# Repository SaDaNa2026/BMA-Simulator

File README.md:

# Hardware

Die Steuerung des BMA-SImulators ist dafür ausgelegt, auf einem Raspberry Pi ausgeführt zu werden. 
Getestet wurde mit einem Raspberry Pi 5B mit 8 GB RAM, die Anwendung sollte allerdings auch ohne Probleme 
auf einem Modell 4 mit 2 GB RAM laufen.

FAT und FBF werden durch den Raspberry Pi über 5V, 3.3V und GND mit Strom versorgt 
und per I2C über die serielle Schnittstelle angesteuert. 
Die Platinen können anhand der beiliegenden KiCAD-Dateien hergestellt werden. 
Zusatzmodule wie eine Blitzleuchte, ein Freischaltelement oder physische Melder können nach Belieben hinzugefügt 
und in die Steuerung eingebunden oder deaktiviert werden.

# Software

## Abhängigkeiten

Zum Ausführen des Python-Scripts müssen Python 3.13 oder neuer und alle in requirements.txt 
definierten Abhängigkeiten installiert sein. 

Bei der Installation der lgpio-Bibliothek ist zu beachten, dass dafür lg auf dem System installiert sein muss. 
lg und die dazugehörige Installationsanleitung sind unter https://github.com/joan2937/lg zu finden.

Auch pygobject benötigt diverse systemweite Bibliotheken, darunter libcairo2-dev und libgtk-4-dev. Die Fehlermeldungen 
bei der Installation sind in der Regel sehr hilfreich, um fehlende Pakete zu identifizieren.

Zusätzlich ist Okular notwendig, um die Hilfedatei anzeigen zu können. Dabei muss okular-extra-backends installiert werden, 
um Markdown-Dateien anzeigen zu können. Natürlich kann auch ein anderer Markdown-Viewer verwendet werden, 
wenn in Application.py die Konstante MARKDOWN_VIEWER entsprechend angepasst wird.  
Falls die Hilfedatei nach PDF konvertiert wird, bieten sich noch mehr Möglichkeiten für die Anzeige. 
Markdown wurde lediglich aufgrund der besseren Integration in das Versionskontrollsystem ausgewählt.

## Desktopeintrag

Es liegt ein Beispiel für eine passende Desktopeintrags-Datei bei. Wenn die in der Datei angegebenen Anpassungen 
erfolgt sind, kann die Datei im entsprechenden Ordner (z.B. /usr/local/share/applications/) abgelegt werden.  
Falls ein Autostart der App erwünscht ist, kann der Desktopeintrag zusätzlich noch in /etc/xdg/autostart/ abgelegt werden.

## Startskript

Da sich alle Python-Pakete und Skripte in einer virtuellen Umgebung befinden, muss diese beim Programmstart erst 
aktiviert werden. Daher ist ein Startskript nötig, das diese Aufgabe übernimmt. Ein entsprechendes Beispiel liegt bei, 
es muss nur der Pfad zum Anwendungsordner angepasst werden. Das Skript kann dann z.B. in /usr/local/bin abgelegt werden.

Für den Fall, dass alle Python-Pakete systemweit installiert sind (ohne virtuelle Umgebung), 
entfällt die Notwendigkeit des Startskripts. Man verliert dann aber natürlich auch alle Vorteile 
der Separierung durch virtuelle Umgebungen.

## Konfiguration von labwc

Falls Raspberry Pi OS (oder ein anderes Betriebssystem mit labwc als Compositor) verwendet wird, 
sollten für ein einheitliches Design der Anwendung Client-Side-Decorations bevorzugt werden. 
Dazu muss in der labwc-Konfigurationsdatei (in der Regel /etc/xdg/labwc/rc.xml) 
die Variable <core><decorations> auf client gesetzt werden. 
Weitere Informationen dazu sind unter https://labwc.github.io/labwc-config.5.html#entry_core_decoration zu finden.  
In diesem Fall empfiehlt es sich auch, in /etc/xdg/labwc/environment die Umgebungsvariable 
QT_WAYLAND_DISABLE_WINDOWDECORATION=0 zu setzen, da ansonsten für Qt-Anwendungen wie Okular 
keine Kopfleiste mehr angezeigt wird.

## Konstanten

In Application.py werden unterhalb der Imports einige Konstanten definiert, mit denen die Anwendung 
an die Umgebung angepasst werden kann. Verfügbar sind:

- Der Standard-Dateipfad für das Öffnen und Speichern von Dateien. Der Pfad sollte existieren, 
    andernfalls funktioniert die Anwendung aber trotzdem.
- Der Markdown-Viewer zur Anzeige der Hilfedatei (einzutragender Name entspricht dem in der Shell).
- Die Standard-Gebäudebeschreibung. Der Zeilenumbruch ist mit \n zu setzen. Die maximale Länge 
    einer Zeile beträgt 20 Zeichen.
- Eine PIN, mit der potenziell destruktive Aktionen wie Speichern oder Rollback gesichert werden. 
    Dies bietet ganz ausdrücklich keine wirkliche Sicherheit, sondern soll nur gegen Fehlbedienung absichern.
- Ein Tupel aller physischen Melder, die angeschlossen sind. Kommentar im Code beachten!  
    Falls keine physischen Melder vorhanden sind, können alle Einträge bis auf den Melder mit Nummer 0/1, 
    welcher intern als Repräsentation der Löschanlage notwendig ist, entfernt werden.
- GPIO-Pin des Relais' für die Blitzleuchte, kann hier auch abgeschaltet werden.

## Integration von Git

Um den Dateistand zurücksetzen zu können, ist Git als Versionskontrollsystem integriert. Bei jedem Speichern
einer Gebäudekonfiguration oder eines Szenarios wird im entsprechenden Verzeichnis ein Repository initialisiert,
falls es nicht bereits eines ist. Anschließend werden alle Änderungen gestaget und committet. 
Über die Funktion "Dateistand zurücksetzen" gibt es dann die Möglichkeit, einen Hard Reset durchzuführen. 
Natürlich ist auch eine manuelle Verwaltung des Repositorys mithilfe von Git möglich.

Diese Integration macht einige Annahmen, die erfüllt werden sollten, um unerwünschte Folgen zu vermeiden:

- Für jede Gebäudekonfiguration mitsamt den dazugehörigen Szenarien existiert ein eigenes Verzeichnis (Gebäudeverzeichnis).
   Dabei können für Szenario-Dateien beliebig viele Unterverzeichnisse mit beliebiger Verschachtelung angelegt werden.
   In diesen Unterverzeichnissen dürfen jedoch keine Gebäudeverzeichnisse enthalten sein, denn:
- Gebäudeverzeichnisse dürfen nicht verschachtelt werden: Dadurch werden alle Änderungen im höhergeordneten Verzeichnis
   der beiden committet, wodurch keine saubere Trennung der Gebäude in den Commit-Messages mehr existiert.
- Es sollte ein eigenes Verzeichnis angelegt werden, das alle Gebäudeverzeichnisse bzw. Verzeichnisse 
   von Gebäudeverzeichnissen enthält. Dieses Verzeichnis sollte der Konstante DEFAULT_FILE_PATH 
   in Application.py entsprechen, wodurch sich die Öffnen- und Speicher-Dialoge direkt im richtigen Verzeichnis befinden.  
   Die Abschottung verhindert, dass andere, "unbeteiligte" Dateien in das Repository 
   aufgenommen werden oder ein Repository in einem Verzeichnis initialisiert wird, wo dies unerwünscht ist.

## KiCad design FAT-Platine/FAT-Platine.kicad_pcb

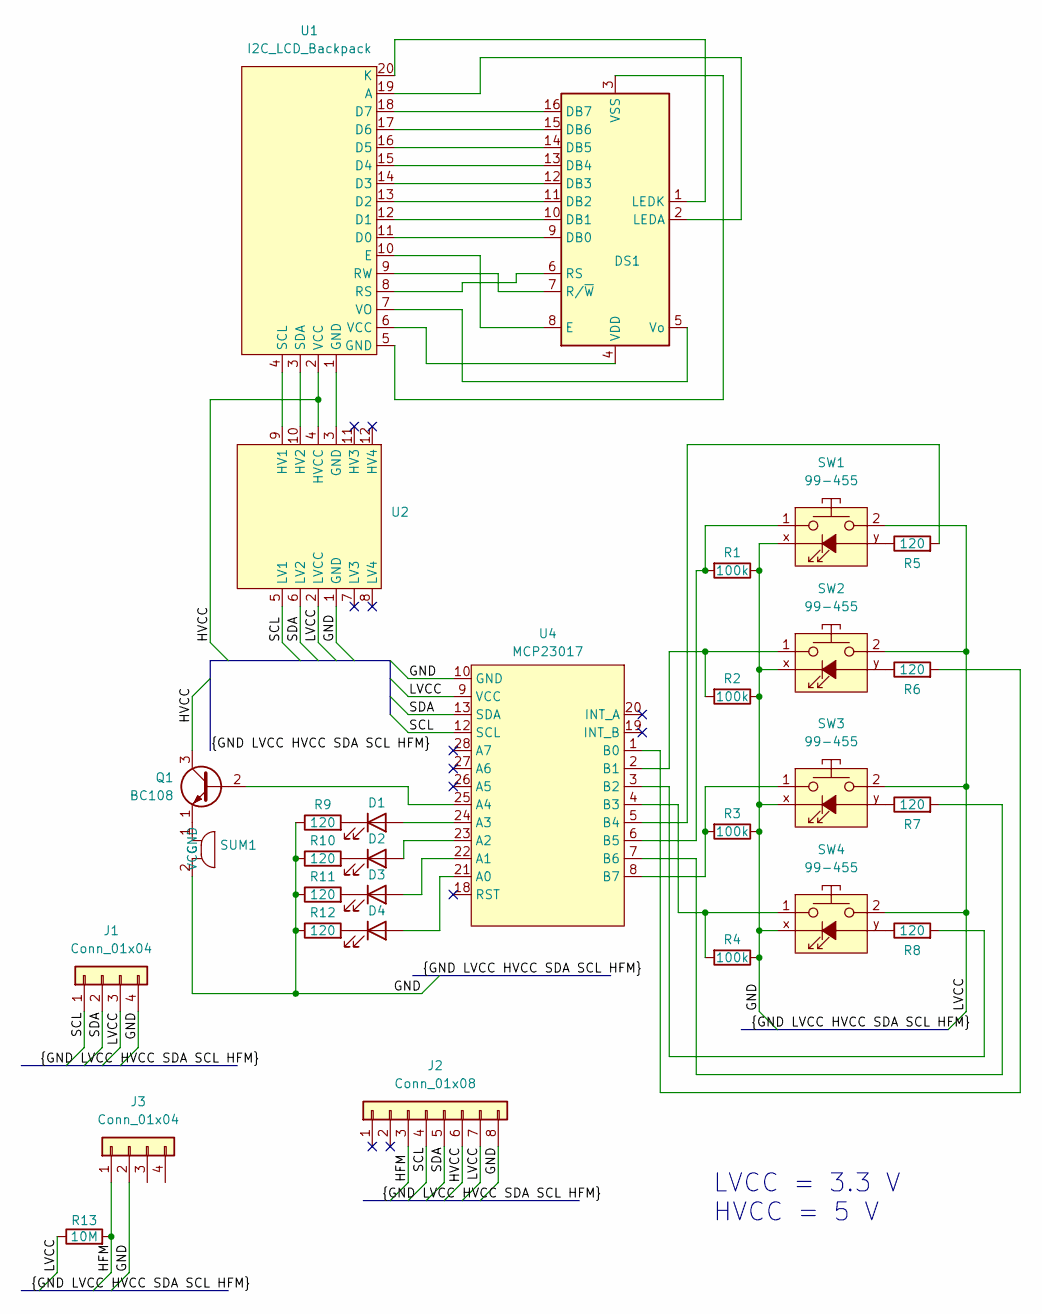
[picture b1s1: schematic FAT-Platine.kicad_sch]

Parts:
D1, D2, D3, D4: LED; LED_D5.0mm
DS1: HD44780; LCD 4x20
J1, J3: Conn_01x04; WAGO_236-404
J2: Conn_01x08; WAGO_236-408
Q1: BC108; TO-18-3
R1, R2, R3, R4: 100k; R_Axial_DIN0207_L6.3mm_D2.5mm_P10.16mm_Horizontal
R5, R6, R7, R8, R9, R10, R11, R12: 120; R_Axial_DIN0207_L6.3mm_D2.5mm_P10.16mm_Horizontal
R13: 10M; R_Axial_DIN0207_L6.3mm_D2.5mm_P10.16mm_Horizontal
SUM1: AL-60SP05
SW1, SW2, SW3, SW4: 99-455; Switch_EAO_4-pin
U1: I2C_LCD_Backpack; LCD_I2C_Backpack
U2: Logic_Level_Converter
U4: MCP23017; MCP23017_Breakout

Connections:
/GND: J1.4, J2.8, J3.2, R1.1, R2.1, R3.1, R4.1, R9.1, R10.1, R11.1, R12.1, SUM1.2 (GND), SW1.x, SW2.x, SW3.x, SW4.x, U2.1 (GND), U4.10 (GND)
/HFM: J2.3, J3.1, R13.2
/HVCC: J2.6, Q1.3 (C), U1.2 (VCC), U2.4 (HVCC)
/LVCC: J1.3, J2.7, R13.1, SW1.2, SW2.2, SW3.2, SW4.2, U2.2 (LVCC), U4.9 (VCC)
/SCL: J1.1, J2.4, U2.5 (LV1), U4.12 (SCL)
/SDA: J1.2, J2.5, U2.6 (LV2), U4.13 (SDA)
unnamed: D1.2 (A), U4.24 (A3)
unnamed: D1.1 (K), R9.2
unnamed: D2.2 (A), U4.23 (A2)
unnamed: D2.1 (K), R10.2
unnamed: D3.2 (A), U4.22 (A1)
unnamed: D3.1 (K), R11.2
unnamed: D4.2 (A), U4.21 (A0)
unnamed: D4.1 (K), R12.2
unnamed: DS1.9 (DB0), U1.11 (D0)
unnamed: DS1.10 (DB1), U1.12 (D1)
unnamed: DS1.11 (DB2), U1.13 (D2)
unnamed: DS1.12 (DB3), U1.14 (D3)
unnamed: DS1.13 (DB4), U1.15 (D4)
unnamed: DS1.14 (DB5), U1.16 (D5)
unnamed: DS1.15 (DB6), U1.17 (D6)
unnamed: DS1.16 (DB7), U1.18 (D7)
unnamed: DS1.8 (E), U1.10 (E)
unnamed: DS1.2 (LEDA), U1.19 (A)
unnamed: DS1.1 (LEDK), U1.20 (K)
unnamed: DS1.6 (RS), U1.8 (RS)
unnamed: DS1.7 (R/~W), U1.9 (RW)
unnamed: DS1.4 (VDD), U1.6 (VCC)
unnamed: DS1.3 (VSS), U1.5 (GND)
unnamed: DS1.5 (Vo), U1.7 (VO)
unnamed: Q1.2 (B), U4.25 (A4)
unnamed: Q1.1 (E), SUM1.1 (VCC)
unnamed: R5.1, SW1.y
unnamed: R6.1, SW2.y
unnamed: R7.1, SW3.y
unnamed: R8.1, SW4.y
unnamed: U1.1 (GND), U2.3 (GND)
unnamed: U1.4 (SCL), U2.9 (HV1)
unnamed: U1.3 (SDA), U2.10 (HV2)
unnamed: R6.2, U4.1 (B0)
unnamed: R2.2, SW2.1, U4.2 (B1)
unnamed: R8.2, U4.3 (B2)
unnamed: R4.2, SW4.1, U4.4 (B3)
unnamed: R5.2, U4.5 (B4)
unnamed: R1.2, SW1.1, U4.6 (B5)
unnamed: R7.2, U4.7 (B6)
unnamed: R3.2, SW3.1, U4.8 (B7)

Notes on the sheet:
LVCC = 3.3 V HVCC = 5 V

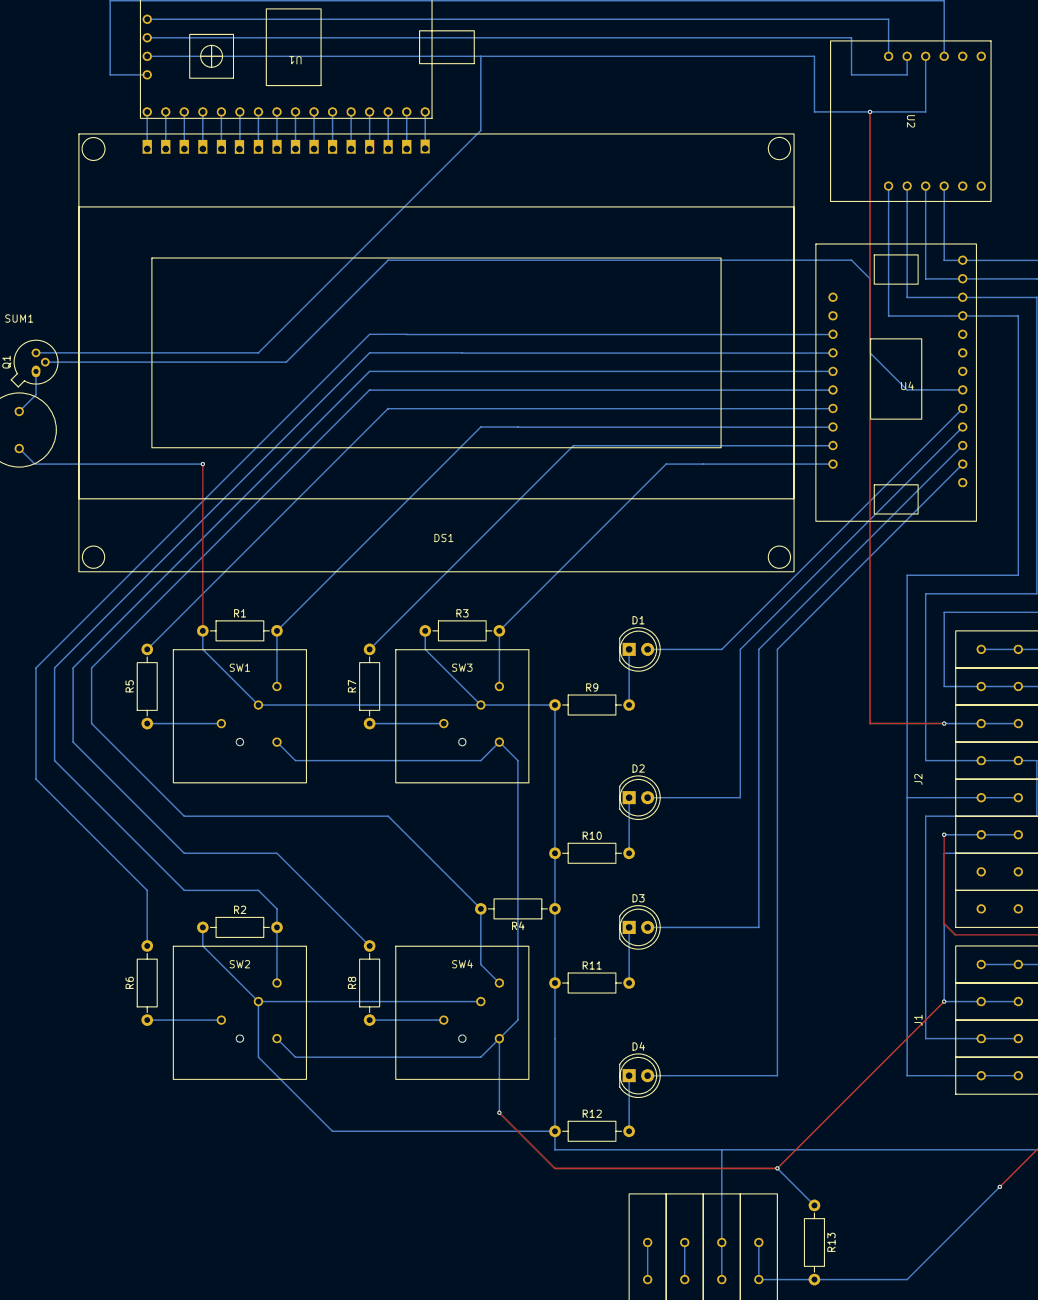
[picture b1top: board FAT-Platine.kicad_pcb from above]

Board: 2 copper layers, 30 parts (0 on the bottom side), 47 nets.

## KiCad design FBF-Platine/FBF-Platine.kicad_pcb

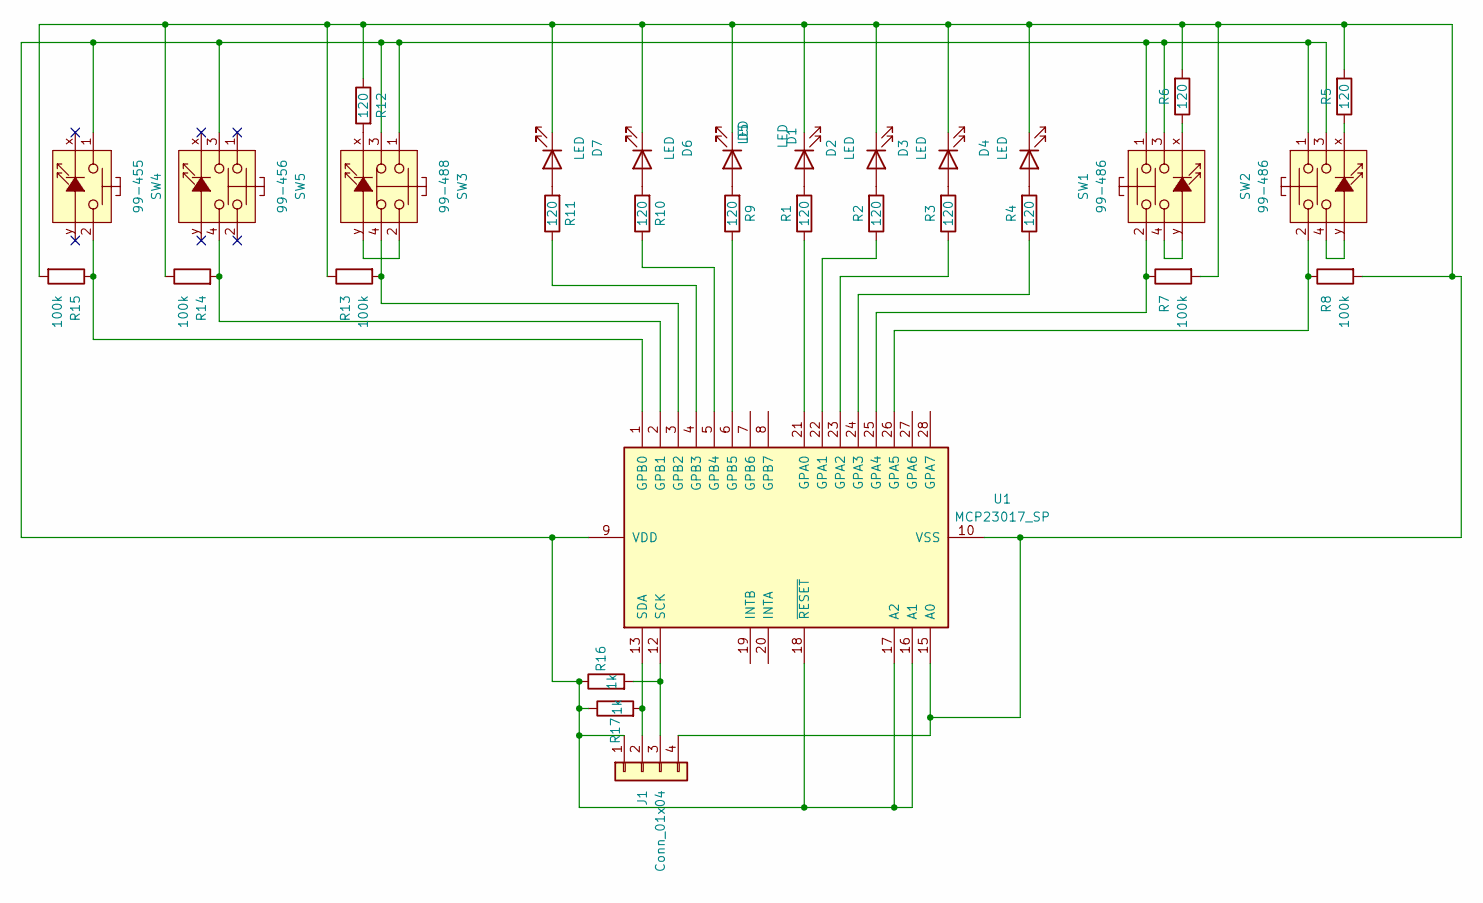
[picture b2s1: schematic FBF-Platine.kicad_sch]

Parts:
D1, D2, D3, D4, D5, D6, D7: LED; LED_D5.0mm
J1: Conn_01x04; WAGO_236-404
R1, R2, R3, R4, R5, R6, R9, R10, R11, R12: 120; R_Axial_DIN0207_L6.3mm_D2.5mm_P10.16mm_Horizontal
R7, R8, R13, R14, R15: 100k; R_Axial_DIN0207_L6.3mm_D2.5mm_P10.16mm_Horizontal
R16, R17: 1k; R_Axial_DIN0207_L6.3mm_D2.5mm_P10.16mm_Horizontal
SW1, SW2: 99-486; Switch_EAO_6-pin
SW3: 99-488; Switch_EAO_6-pin
SW4: 99-455; Switch_EAO_4-pin
SW5: 99-456; Switch_EAO_6-pin
U1: MCP23017_SP; DIP-28_W7.62mm

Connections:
unnamed: D1.2 (A), R1.2
unnamed: D1.1 (K), D2.1 (K), D3.1 (K), D4.1 (K), D5.1 (K), D6.1 (K), D7.1 (K), J1.4, R5.2, R6.2, R7.2, R8.2, R12.1, R13.1, R14.1, R15.2, U1.10 (VSS), U1.15 (A0)
unnamed: D2.2 (A), R2.2
unnamed: D3.2 (A), R3.2
unnamed: D4.2 (A), R4.2
unnamed: D5.2 (A), R9.2
unnamed: D6.2 (A), R10.2
unnamed: D7.2 (A), R11.2
unnamed: J1.1, R16.1, R17.1, SW1.1, SW1.3, SW2.1, SW2.3, SW3.1, SW3.3, SW4.1, SW5.3, U1.9 (VDD), U1.16 (A1), U1.17 (A2), U1.18 (~RESET)
unnamed: J1.2, R17.2, U1.13 (SDA)
unnamed: J1.3, R16.2, U1.12 (SCK)
unnamed: R5.1, SW2.x
unnamed: R6.1, SW1.x
unnamed: R12.2, SW3.x
unnamed: SW1.4, SW1.y
unnamed: SW2.4, SW2.y
unnamed: SW3.2, SW3.y
unnamed: R1.1, U1.21 (GPA0)
unnamed: R2.1, U1.22 (GPA1)
unnamed: R3.1, U1.23 (GPA2)
unnamed: R4.1, U1.24 (GPA3)
unnamed: R7.1, SW1.2, U1.25 (GPA4)
unnamed: R8.1, SW2.2, U1.26 (GPA5)
unnamed: R15.1, SW4.2, U1.1 (GPB0)
unnamed: R14.2, SW5.4, U1.2 (GPB1)
unnamed: R13.2, SW3.4, U1.3 (GPB2)
unnamed: R11.1, U1.4 (GPB3)
unnamed: R10.1, U1.5 (GPB4)
unnamed: R9.1, U1.6 (GPB5)

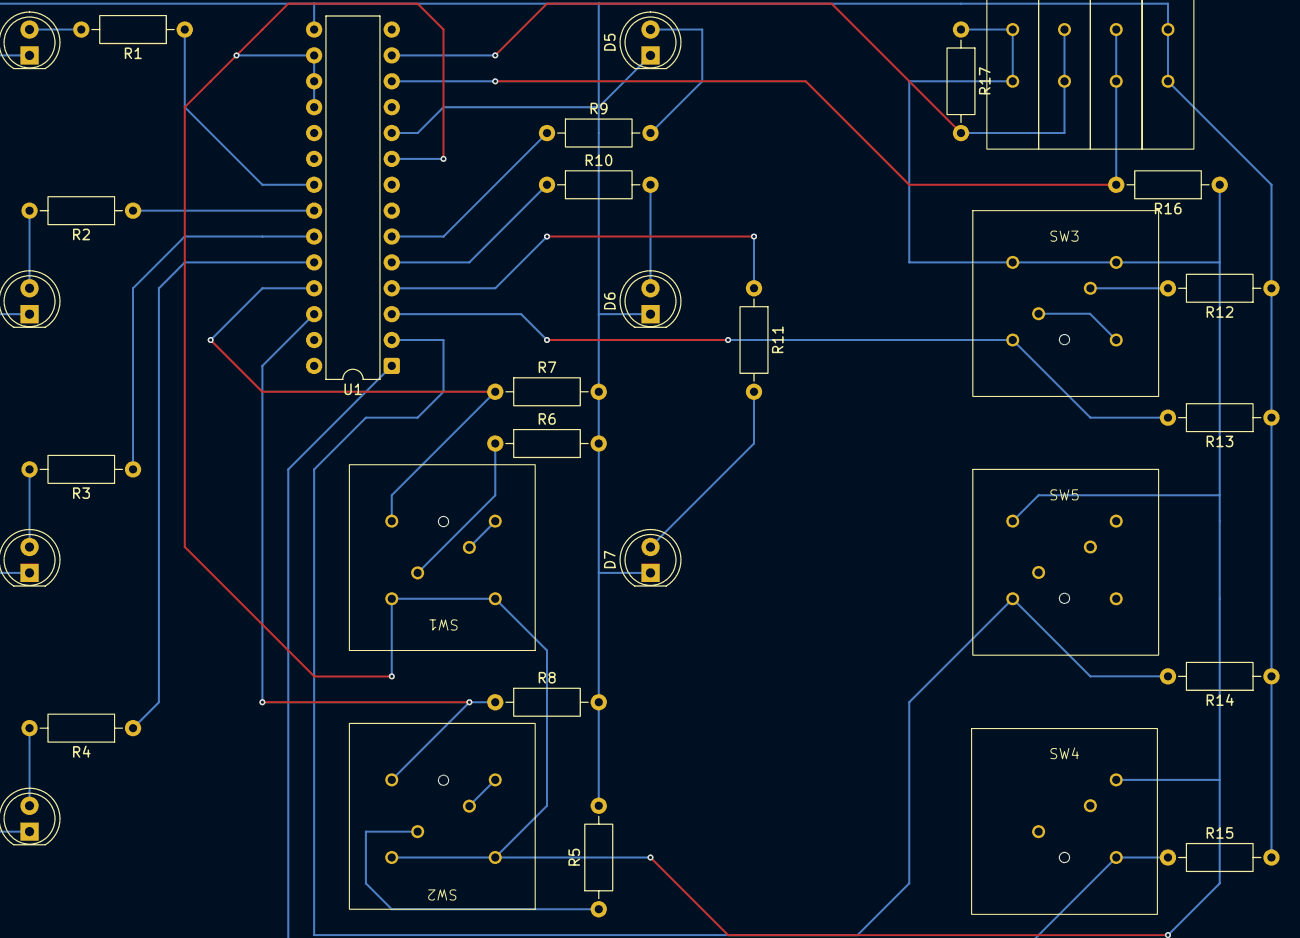
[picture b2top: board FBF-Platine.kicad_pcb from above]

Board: 2 copper layers, 31 parts (0 on the bottom side), 29 nets.

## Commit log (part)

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2025-11-03 Sehr frühe, experimentelle Testversion zum Management von Meldern als Klassen und der dynamischen Erstellung von Meldern.
2025-11-04 Melderlinien und Melder werden nun in einem dictionary gespeichert, sodass jedes Objekt mit der Nummer der Melderlinie und des Melders aufgerufen werden kann. Es können dadurch auch arbiträre Melder(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
2025-11-05 Funktionalität zum Speichern und Öffnen wurde vorerst entfernt. Die neue Klassse Building für Eigenschaften des Gebäudes wrde hinzugefügt. Eigenschaften und Zugehörigkeiten werden nicht mehr in einem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
2025-11-06 Refactoring: Alle globalen Funktionen wurden in die Klasse MainWindow verschoben. Die Klasse und Funktionen für den Öffnen-Dialog wurden logischer benannt.
    Fix: Beim Laden aus der Datei wurden in building.circuit_dict bisher strings für die keys geschrieben, was das Löschen unmöglich machte. Nun werden die keys korrekt als integer geschrieben.
2025-11-24 Ein Bug wurde entfernt, durch den bei jedem Öffnen des Kontextmenüs der delete_circuit_button erneut mit der entsprechenden Funktion verbunden wurde. Dadurch wurde bei mehrmaligem Öffnen des Kontextm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
2025-11-25 Kleinere Verbesserungen. Der unnötige Parameter "button" wurde aus den Methoden on_save_clicked und on_open_clicked entfernt, um Vorbereitungen für den Wechsel zu Gtk Actions vorzubereiten.
2025-11-26 Wenn das Fenster zum Erstellen von Meldern bzw. Melderlinien geöffnet ist, kann nun das Hauptfenster keinen Fokus mehr erhalten. Dies verhindert unerwünschte Effekte, wie z.B. dass mehrere solcher Fe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
2025-11-27 Die Buttons zum Speichern und Öffnen wurden in ein Menü unter dem MenuButton "Datei" verschoben.
2025-11-27 Zur Vorbereitung auf die Speicherung von Szenarien wurden die Funktionen zum Speichern und Laden offener gestaltet, sodass verschiedene dictionaries gespeichert werden können. Zwischen diesen wird du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
2025-12-01 Es können nun Szenarien gespeichert und geladen werden. Dafür wird beim Öffnen einer .scenario-Datei im selben Verzeichnis nach einer .building Datei gesucht. Falls nicht exakt eine gefunden wird, wi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
2025-12-02 Größeres Refactoring: Alle Klassen wurden zur besseren Strukturierung in separate Dateien verschoben. Building wird nun nicht mehr instanziert, sondern enthält nur Klassenattribute. Das vereinfacht d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
    Ein Bug wurde behoben, bei dem in on_edit_detector_clicked der Name der EditDetectorWindow-Instanz mit dem edit_detector_callback übereinstimmte.
2025-12-03 Refactoring: Die actions sind nun in ActionGroups gruppiert. So können sie eleganter hinzugefügt und enabled/disabled werden. Daher werden actions jetzt anstatt von "win.{action_name}" mit "{action_g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
2025-12-05 Nicht funktionale Zwischenversion. Das gesamte Projekt wird auf das Model View Controller Konzept umgestellt. dafür wurde die Datei Building in Model umbenannt und dient nun als Model, um den Zustand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
2025-12-09 Model_test wurde aufgeräumt und erweitert, um neue Methoden zu testen.
2025-12-10 Weitere Tests für FileOperations wurden hinzugefügt.
2025-12-12 Die Länge der Nummern von Meldergruppen und Meldern wurde auf die Norm angepasst. Refactoring: DefineObjectWindows prüfen nun nicht mehr selbst auf falsche Eingaben, sondern überlassen diese Aufgabe 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
2026-01-15 Unten im Fenster wird nun eine Liste der aktiven Melder in der Reihenfolge ihrer Auslösung angezeigt, genau wie auf dem FAT. model_test wurde an die vor einigen Versionen geänderten Limits der Längen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
2026-01-19 LEDController wurde hinzugefügt, um die LEDs anzusteuern und blinken zu lassen. Diese Funktion wurde allerdings noch nicht in den Controller übernommen.
2026-01-20 Die Taster zum Scrollen durch die Meldungen funktionieren nun zuverlässiger, auch wenn während des Betriebs Melder(-gruppen) gelöscht werden. Die LED eines Tasters blinkt, sofern, Meldungen in die je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
2026-01-21 Winziger Fix: Die Fehlermeldung beim Öffnen einer Szenariodatei mit Meldern, die in der Gebäudedatei nicht vorkommen, zeigt wieder korrekt die Nummer des Melders und der Meldergruppe an, der fehlerha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
2026-01-21 on_detector_switch_toggled setzt nun den alarm_status des Melders im Model entsprechend dem Status der action, nicht dem vorherigen Wert im Model. Dadurch ist Konsistenz zwischen dem View und Model g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
2026-01-21 Es wird nun gespeichert, welche Melder abgeschaltet sind.
2026-01-27 Beim Speichern wird die Änderung nun automatisch in einem Git-Repository commited. Falls das Verzeichnis noch kein Repository ist, wird eines erstellt.
2026-01-29 Vor dem git Reset erscheint nun noch ein Warnfenster, das auf den bevorstehenden Datenverlust hinweist.
2026-02-03 Das Bearbeiten derGebäudebeschreibung wurde ebenfalls zu Operations verschoben.
2026-02-04 Die Abschaltung von Meldern kann nun auch rückgängig gemacht werden.
2026-02-05 Abgeschaltete Melder werden nun in einer zweitetn Konsole neben den ausgelösten Meldern angezeigt.
2026-02-13 Alle LEDs auf dem FBF können nun über ein Einstellungs-Fenster angesteuert werden. Die entsprechende Einstellung wird im Szenario gespeichert und geladen.
2026-03-02 Es wurde ein Bug behoben, der dazu führte, dass Commits, die Dateien hinzufügten, als Löschen von Dateien angezeigt wurden. Dies lag daran, dass der diff des Commits gegen sein parent bestimmt wurde 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
2026-03-02 README.md enthält nun die deutsche Bedienungsanleitung.
2026-03-04 Alle modalen Fenster sind nun nicht mehr in der Größe veränderlich. Das führt zu konsistenter Darstellung.
2026-03-04 Das (noch leere) ShorcutsWindow wurde entfernt, da die Unterstützung dafür mit der nächsten Gtk-Version endet. Außerdem sind alle Tastenkürzel neben den GUI-Bedienflächen sichtbar. Es wurden Tastenkü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
2026-03-05 Die Hilfedatei wurde erweitert und Fehler darin korrigiert.
2026-03-05 Melder können nun über das Kontextmenü zur Historie hinzugefügt werden. Die Aktion lässt sich rückgängig machen.
2026-03-06 Auch bei Rückgängig machen von Abschaltung und Historie behalten jetzt alle Melder ihre korrekte Position in der Liste.
2026-03-09 Die Historie lässt sich jetzt über einen Eintrag im Bearbeiten-Menü leeren. Die Aktion kann rückgängig gemacht werden. Die Hilfedatei wurde entsprechend der neuen Funktionen angepasst. Im Model wurde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
2026-03-10 ÜE-Test funktioniert jetzt.
2026-03-11 Das Anwendungsfenster hat rechts eine Seitenleiste zur Anzeige und Bearbeitung der Szenariobeschreibung erhalten. Diese Beschreibung wird gespeichert und geladen. Die Hilfedatei enthält nun einen Abs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
2026-03-16 Die eingestellte Historienzeit wird nun in der Historie und der entsprechenden Konsole angezeigt. Das Model und seine Tests wurden angepasst, um immer einen korrekten Zeit-String zu liefern. Es wurde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
2026-03-16 Die Historienzeit-Einstellungen werden jetzt im Szenario gespeichert und geladen. Die Zeit in der Historien-Konsole wird bei Änderungen an der Einstellung nun neu geladen, um immer die korrekte Zeit 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
2026-03-18 Je ein Beispiel für ein geeignetes Startskript und einen Desktopeintrag wurden hinzugefügt, um die Installation der Anwendung auf anderen Systemen zu erleichtern. README.md wurde entsprechend erweite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
2026-03-19 Es kann nun ein Freischaltelement an einen GPIO-Pin angeschlossen werden. Wenn dieser Taster gedrückt wird, wird der virtuelle Melder 0/0 mit der Beschreibung "Freischaltelement" hinzugefügt und ausg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
2026-03-26 Informationen zur Einstellung für die Blitzleuchte wurden zur Hilfedatei hinzugefügt. Der Summer "blinkt" jetzt, anstatt dauerhaft aktiv zu sein.
2026-03-26 Der Taster "Summer ab" blinkt nun, wenn der Summer aktiv ist. Ein Bug wurde behoben, durch den Änderungen an "Blitzleuchte bei Alarm aktivieren" sich auf einen bereits aktiven Alarm nicht auswirkten.
2026-04-01 Bugfix für den Bugfix: Das Ändern der Beschreibung eines in der Historie befindlichen Melders hatte durch den letzten Commit nicht mehr die angezeigte Beschreibung verändert. Das ist behoben.
2026-04-14 Die Ordner mit den KiCAD-Dateien und PDF-Schaltplänen für die Platinen wurden hinzugefügt.
2026-04-14 Klarstellung zum Standard-Dateipfad
2026-04-14 Anpassung der Entwickler-Email
2026-04-14 Ein weiterer WAGO-Klemmenverbund und Pullup-Widerstand wurde zur Platine hinzugefügt, um den Handfeuermelder anschließen zu können.
2026-04-15 Bugfixes für Fehler beim Zurücksetzen der BMA in Zusammenhang mit dem Handfeuermelder.
2026-04-15 Weiterer Bugfix in clear_alarms: Zurücksetzen der BMA führt nicht mehr dazu, dass Einträge in den undo_stack gepusht werden.
2026-04-15 Die Exception bei inkorrekter Anzahl an .building-Dateien wird nun korrekt durchgereicht und eine Fehlermeldung angezeigt.
2026-04-16 Neue Funktion zur Bestimmung der Dateiendung.
2026-04-16 Entfernung der drei Punkte hinter Hilfe und Einstellungen
2026-04-16 Update der FAT-Platinendateien, um die Änderung des Widerstandswerts zu reflektieren.
2026-04-16 CONTRIBUTING.md hinzugefügt
2026-04-17 Wert von FSE_PIN angepasst
2026-04-21 Bugfix: first_message_shown und last_message_shown prüfen nun, ob die Liste der Melder in der Historie leer ist, bevor sie darauf zugreifen. Dies verhindert Fehler durch Zugriffe auf Elemente einer l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
2026-04-21 Refactring: Nutzen der getter-Methode anstatt Direktzugriff auf model.circuit_dict
2026-04-23 Unterstützung für zweizeilige Gebäudebeschreibungen wurde hinzugefügt. Die Beschreibung ist jetzt jeweils in der Zeile zentriert ausgerichtet.
2026-04-23 Dem README wurde ein Eintrag zur neuen Konstante DEFAULT_BUILDING_DESCRIPTION hinzugefügt.
2026-04-23 Bei der Eingabe der PIN werden die Zeichen nun verschleiert und es gibt keine maximale Länge mehr.
2026-04-24 Tests für set_detector_alarm_status mit list_index außerhalb der Länge der Liste hinzugefügt
2026-04-24 Bugfix: Beim Zurückstellen muss extinguisher_triggered auf False gesetzt werden.
2026-04-24 Bugfix: window.circuit_dict() war nach delete_all() nicht leer, da nur die Werte und nicht auch die Schlüssel des dictionary gelöscht wurden.
2026-05-05 Bugfix des Bugfix: Entfernen eines fehlerhaft von der IDE automatisch hinzugefügten Imports, der zu einer circular Dependency führte.
2026-05-07 Frühe, völlig unfertige Version eines Szenario-Browsers und der nötigen Unterstützungsmethoden in bestehenden Klassen.
2026-05-08 Der Filetree wird nun bei der Initialisierung gefüllt und verlinkt zu den korrekten Szenarien. Dynamische Anpassung an Filter fehlen noch.
2026-05-11 Tastenkürzel zum Öffnen des Szenario-Browsers hinzugefügt
2026-05-12 Die Anzeige der Szenariobeschreibung und das Filtern nach Tags funktioniert jetzt
2026-05-12 Refactoring: Das Auswahlmenü für die Tags (TagSelector) wurde aus ScenarioBrowser in eine eigene Klasse verschoben, um an anderen Stellen wiederverwendet werden zu können
2026-05-12 Beim Laden eines Szenarios zeigt der TagSelector im MainWindow jetzt die Tags des Szenarios
2026-05-12 Bugfix: Es ist sinnvoll, tasächlich alle Elemente in tag_object_list zu entfernen.
2026-05-13 Umstellung der Menüs in der HeaderBar zur besseren Organisation
2026-05-18 Refactoring: Die an vielen Stellen redundant implementierte ConfirmationBox ist nun eine eigene Klasse.
2026-05-19 Feature: TagDefinitionWindow hinzugefügt. Aktuell nur Anzeige ohne Funktion.
2026-05-20 Feature: TagDefinitionWindow bietet nun Undo/Redo für alle Aktionen außer dem Ändern eines Tag-Namens (wird intern von Gtk gehandelt und nur beim Speichern abgefragt)
2026-05-21 Unterstützung des direkten Öffnens einer Datei durch das "open"-Signal. Entsprechende Anpassungen an Desktop-Eintrag und Start-Skript, um die Datei als Argument beim Start zu übergeben.
2026-05-27 Revert "Formatierung angepasst und teils eindeutigere Beschreibung"
    This reverts commit 6599450b212bacc6332a9d857e3724dd4b25bbc2.
2026-06-11 Das Zurückstellen der BMA leert nun den Undo und Redo Stack, um inkonsistente Zustände zu verhindern.
2026-06-12 Bugfix: Aktivierte permanente Melder (z.B. Löschanlage) wurden im Szenario gespeichert. Das führte zu Problemen, da sie in der Gebäudedatei nicht vorhanden sind. Daher kann nun bei BuildingModel.get_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
2026-06-12 Reste der hardkodierten Implementation der Löschanlage entfernt
